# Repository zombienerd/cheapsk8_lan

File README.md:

CheapSk8 LAN is an 8-bit ISA network card based on the RTL 8019AS chip.  

This project was created for cost savings over purchasing older cards on eBay or building other similar projects.  This project was done by reverse engineering a 16-bit RTL8019AS board, and finding the bits needed in the datasheet to turn off 16 bit mode.

By sourcing the MagJack and RTL8019AS from Aliexpress, the 93LC46 from eBay, and the discretes from Mouser or Digikey, and the PCB from JLCPCB, the bill of materials for a board is only about $7.50 when you build 20 or more.

Link to MagJacks: https://www.aliexpress.com/item/32845892783.html

Link to RTL8019AS: https://www.aliexpress.com/item/4000545658898.html

Link to 93LC46 SMT 1k PROM: https://www.ebay.com/itm/133483822518

Mouser-bom.ods is a spreadsheet for the other discretes needed once you've sourced the above 3 items.

Entire project is licensed under CC BY-SA 4.0: https://creativecommons.org/licenses/by-sa/4.0/  You may copy/modify/distribute this project as you see fit as long as my name and project name are listed, and the license is carried forward to your project.

Drivers / Configuration:

In the Drivers/Config folder, you will find the following software:

NE2000.COM - Modified Crynwr Packet Driver for 8-bit NE2000 based cards.  Modified by Dan over on the VCF Forums (https://forum.vcfed.org/index.php?threads/ne2000-packet-drivers-for-8-bit-slots.41507/)
NE2000.ASM - Associated file to NE2000.COM
PG9018.EXE - Initial programming tool for the card.
8019AS.CFG - Initial Configuration file for the card (Read ahead carefully)
RSET8019.EXE - Configuration tool for the card.

Before configuration, edit 8019AS.CFG and add a MAC address to the 1st line.  If you are building more than one card, you should ensure that no two cards have the same address.  You can use one of the Private MAC address Allocations, known as "Locally Administered Address Ranges" and will not be used by mainstream devices or vendors. The MAC addresses in these ranges can be safely used, as long as they are unique within your network:

x2-xx-xx-xx-xx-xx

x6-xx-xx-xx-xx-xx

xA-xx-xx-xx-xx-xx

xE-xx-xx-xx-xx-xx

Each pair can be any hexadecimal number. You use space instead of - in the cfg file.  For example:  52 0a 1b 3c 4e 5f 00 or 12 1a 2b 3c 4d 5e

You should set your IOBASE to a free IO address (300 is default), IRQ (2 is default), and enable or disable the bootrom.  Beware conflicts with XT-IDE, or certain Sound Card/Midi Devices.  

Once you have edited the file to your liking, boot your machine with no memory managers (EMM386 or HIMEM.sys) and run PG8019.EXE  - this will program the card and tick up the MAC address and serial number incrementally in the 8019as.cfg file, so you don't have to edit to run it on subsequent cards.

Once the card is programmed, you can use RSET8019.EXE at any time to change the Base address and IRQ if you plan to change your system configuration.

Thank you to Sergey Kiselev for hosting the 8019 programming tools that I have copied over for this project.  Check out his very similar project (that's a lot more polished, and a bit more high class) over at https://github.com/skiselev/isa8_eth

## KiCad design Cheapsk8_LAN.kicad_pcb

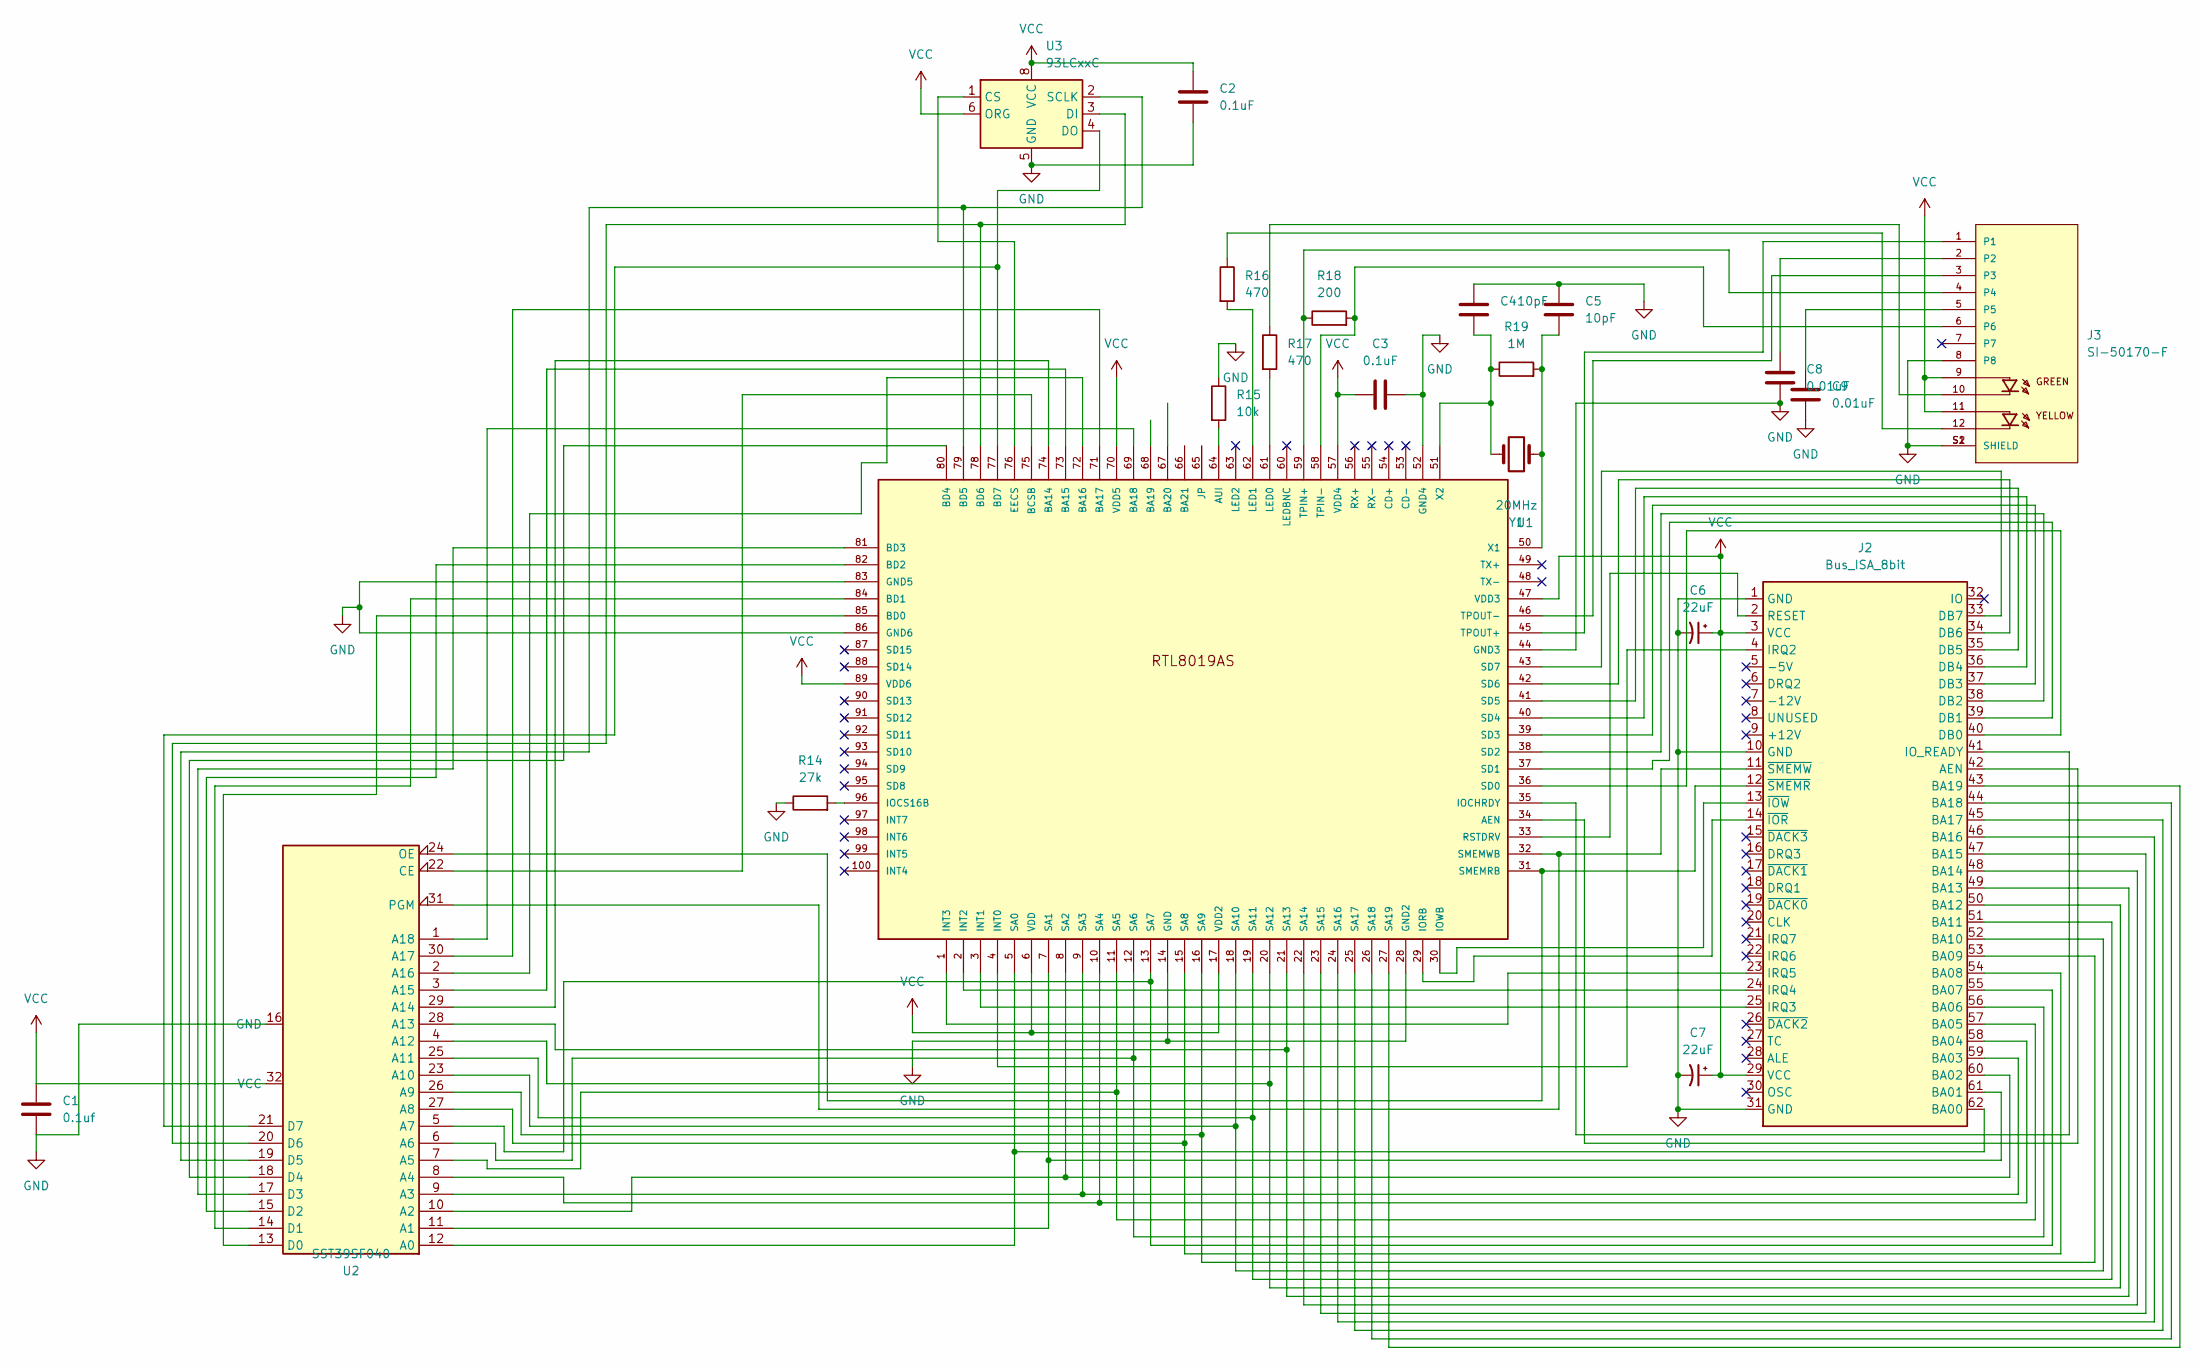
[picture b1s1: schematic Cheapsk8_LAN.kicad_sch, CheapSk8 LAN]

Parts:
C1: 0.1uf; C_0201_0603Metric_Pad0.64x0.40mm_HandSolder
C2, C3: 0.1uF; C_0201_0603Metric_Pad0.64x0.40mm_HandSolder
C4, C5: 10pF; C_0201_0603Metric_Pad0.64x0.40mm_HandSolder
C6, C7: 22uF; CP_Radial_D5.0mm_P2.00mm
C8, C9: 0.01uF; C_0201_0603Metric_Pad0.64x0.40mm_HandSolder
J2: Bus_ISA_8bit; BUS_PC
J3: SI-50170-F; BEL_SI-50170-F; PARTREV 07
R14: 27k; R_0603_1608Metric_Pad0.98x0.95mm_HandSolder
R15: 10k; R_0603_1608Metric_Pad0.98x0.95mm_HandSolder
R16, R17: 470; R_0603_1608Metric_Pad0.98x0.95mm_HandSolder
R18: 200; R_0603_1608Metric_Pad0.98x0.95mm_HandSolder
R19: 1M; R_0603_1608Metric_Pad0.98x0.95mm_HandSolder
U1: RTL8019AS
U2: SST39SF040; DIP-32_W15.24mm
U3: 93LCxxC; DIP-8_W7.62mm_SMDSocket_SmallPads
Y1: 20MHz; Crystal_HC49-U_Horizontal

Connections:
GND: C1.2, C2.2, C3.2, C4.1, C5.1, C6.2, C7.2, C8.2, C9.2, J2.1 (GND), J2.10 (GND), J2.31 (GND), J3.8, J3.S1 (SHIELD), J3.S2 (SHIELD), R14.1, R15.1, U1.14 (GND), U1.28 (GND2), U1.44 (GND3), U1.52 (GND4), U1.83 (GND5), U1.86 (GND6), U2.16 (GND), U3.5 (GND)
unnamed: C8.1, J3.2
unnamed: C9.1, J3.5
unnamed: J3.10, R17.1
unnamed: J3.12, R16.1
unnamed: J2.23 (IRQ5), U1.1 (INT3)
unnamed: J2.24 (IRQ4), U1.2 (INT2)
unnamed: J2.25 (IRQ3), U1.3 (INT1)
unnamed: J2.4 (IRQ2), U1.4 (INT0)
unnamed: J2.62 (BA00), U1.5 (SA0), U2.12 (A0)
unnamed: J2.61 (BA01), U1.7 (SA1), U2.11 (A1)
unnamed: J2.60 (BA02), U1.8 (SA2), U2.10 (A2)
unnamed: J2.59 (BA03), U1.9 (SA3), U2.9 (A3)
unnamed: J2.58 (BA04), U1.10 (SA4), U2.8 (A4)
unnamed: J2.57 (BA05), U1.11 (SA5), U2.7 (A5)
unnamed: J2.56 (BA06), U1.12 (SA6), U2.6 (A6)
unnamed: J2.55 (BA07), U1.13 (SA7), U2.5 (A7)
unnamed: J2.54 (BA08), U1.15 (SA8), U2.27 (A8)
unnamed: J2.53 (BA09), U1.16 (SA9), U2.26 (A9)
unnamed: J2.52 (BA10), U1.18 (SA10), U2.23 (A10)
unnamed: J2.51 (BA11), U1.19 (SA11), U2.25 (A11)
unnamed: J2.50 (BA12), U1.20 (SA12), U2.4 (A12)
unnamed: J2.49 (BA13), U1.21 (SA13), U2.28 (A13)
unnamed: J2.48 (BA14), U1.22 (SA14)
unnamed: J2.47 (BA15), U1.23 (SA15)
unnamed: J2.46 (BA16), U1.24 (SA16)
unnamed: J2.45 (BA17), U1.25 (SA17)
unnamed: J2.44 (BA18), U1.26 (SA18)
unnamed: J2.43 (BA19), U1.27 (SA19)
unnamed: J2.14 (~IOR), U1.29 (IORB)
unnamed: J2.13 (~IOW), U1.30 (IOWB)
unnamed: J2.12 (~SMEMR), U1.31 (SMEMRB), U2.24 (OE)
unnamed: J2.11 (~SMEMW), U1.32 (SMEMWB), U2.31 (PGM)
unnamed: J2.2 (RESET), U1.33 (RSTDRV)
unnamed: J2.42 (AEN), U1.34 (AEN)
unnamed: J2.41 (IO_READY), U1.35 (IOCHRDY)
unnamed: J2.40 (DB0), U1.36 (SD0)
unnamed: J2.39 (DB1), U1.37 (SD1)
unnamed: J2.38 (DB2), U1.38 (SD2)
unnamed: J2.37 (DB3), U1.39 (SD3)
unnamed: J2.36 (DB4), U1.40 (SD4)
unnamed: J2.35 (DB5), U1.41 (SD5)
unnamed: J2.34 (DB6), U1.42 (SD6)
unnamed: J2.33 (DB7), U1.43 (SD7)
unnamed: J3.1, U1.45 (TPOUT+)
unnamed: J3.3, U1.46 (TPOUT-)
unnamed: C5.2, R19.2, U1.50 (X1), Y1.1
unnamed: C4.2, R19.1, U1.51 (X2), Y1.2
unnamed: J3.6, R18.2, U1.58 (TPIN-)
unnamed: J3.4, R18.1, U1.59 (TPIN+)
unnamed: R17.2, U1.61 (LED0)
unnamed: R16.2, U1.62 (LED1)
unnamed: R15.2, U1.64 (AUI)
unnamed: U1.69 (BA18), U2.1 (A18)
unnamed: U1.71 (BA17), U2.30 (A17)
unnamed: U1.72 (BA16), U2.2 (A16)
unnamed: U1.73 (BA15), U2.3 (A15)
unnamed: U1.74 (BA14), U2.29 (A14)
unnamed: U1.75 (BCSB), U2.22 (CE)
unnamed: U1.76 (EECS), U3.1 (CS)
unnamed: U1.77 (BD7), U2.21 (D7), U3.4 (DO)
unnamed: U1.78 (BD6), U2.20 (D6), U3.3 (DI)
unnamed: U1.79 (BD5), U2.19 (D5), U3.2 (SCLK)
unnamed: U1.80 (BD4), U2.18 (D4)
unnamed: U1.81 (BD3), U2.17 (D3)
unnamed: U1.82 (BD2), U2.15 (D2)
unnamed: U1.84 (BD1), U2.14 (D1)
unnamed: U1.85 (BD0), U2.13 (D0)
unnamed: R14.2, U1.96 (IOCS16B)
VCC: C1.1, C2.1, C3.1, C6.1, C7.1, J2.3 (VCC), J2.29 (VCC), J3.9, J3.11, U1.6 (VDD), U1.17 (VDD2), U1.47 (VDD3), U1.57 (VDD4), U1.70 (VDD5), U1.89 (VDD6), U2.32 (VCC), U3.6 (ORG), U3.8 (VCC)

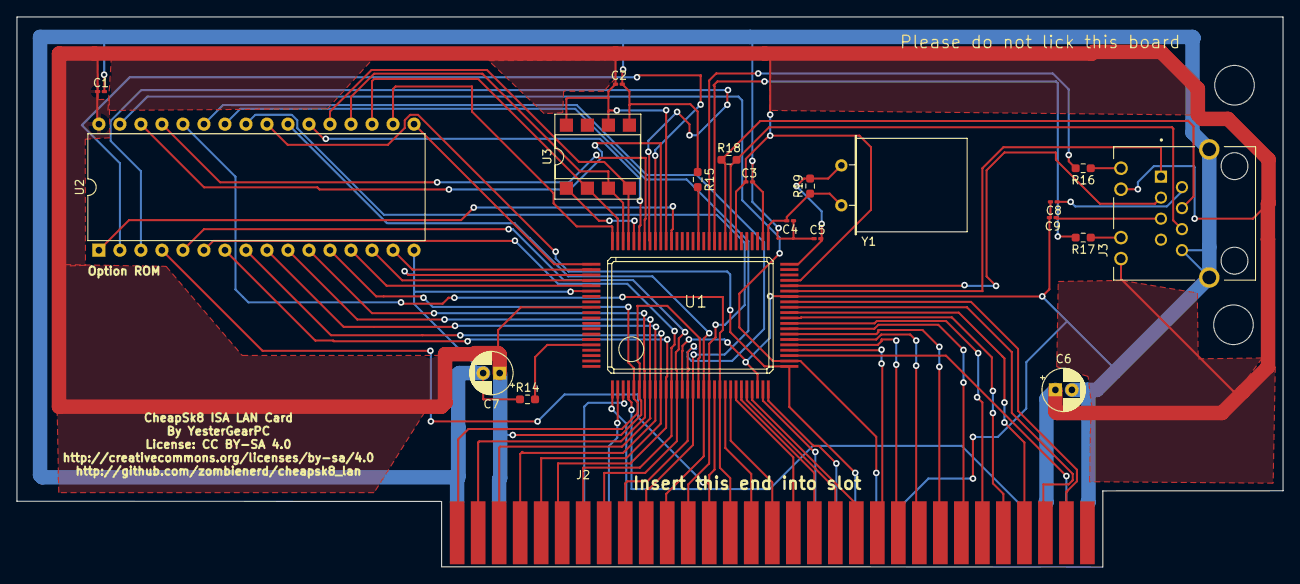
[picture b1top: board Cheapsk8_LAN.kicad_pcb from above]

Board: 2 copper layers, 153.1 x 66.5 mm, 21 parts (0 on the bottom side), 70 nets.

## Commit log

2022-05-09 Changes to be committed: modified: Cheapsk8_LAN.kicad_pcb modified: Cheapsk8_LAN.kicad_prl modified: Cheapsk8_LAN.kicad_pro modified: Cheapsk8_LAN.kicad_sch
    Untracked files:
    Cheapsk8_LAN.csv
    Cheapsk8_LAN.net
    Cheapsk8_LAN.xml
    fp-info-cache
    fp-lib-table
2022-05-09 new file: Cheapsk8_LAN.csv new file: Cheapsk8_LAN.net new file: Cheapsk8_LAN.xml new file: gerber/Cheapsk8_LAN-B_Cu.gbr new file: gerber/Cheapsk8_LAN-B_Mask.gbr new file: gerber/Cheapsk8_LAN-B_Paste.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
2022-05-10 new file: drivers-config/8019AS.CFG new file: drivers-config/8019AS.CFG.ORIG new file: drivers-config/COPYING.DOC new file: drivers-config/NE2000.ASM new file: drivers-config/NE2000.COM new file: dri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
2022-05-10 modified: drivers-config/8019AS.CFG deleted: drivers-config/8019AS.CFG.ORIG deleted: drivers-config/COPYING.DOC
2022-05-10 modified: drivers-config/8019AS.CFG
2022-05-10 new file: mouser-bom.ods
2022-05-10 modified: Cheapsk8_LAN.kicad_pcb modified: Cheapsk8_LAN.kicad_prl modified: gerber/Cheapsk8_LAN-B_Cu.gbr modified: gerber/Cheapsk8_LAN-B_Mask.gbr modified: gerber/Cheapsk8_LAN-B_Paste.gbr modified: g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
2022-05-12 modified: gerber/Cheapsk8_LAN-B_Cu.gbr modified: gerber/Cheapsk8_LAN-B_Mask.gbr modified: gerber/Cheapsk8_LAN-B_Paste.gbr modified: gerber/Cheapsk8_LAN-B_Silkscreen.gbr modified: gerber/Cheapsk8_LAN-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

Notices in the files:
Cheapsk8_LAN.kicad_pcb:
License: CC BY-SA 4.0
http://creativecommons.org/licenses/by-sa/4.0
